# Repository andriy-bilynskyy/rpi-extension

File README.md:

# Raspberry Pi - Radioberry interconnection board

This project is a PCB design to create SDR transceiver using
Raspberry Pi and Radioberry boards. Simple connection of boards
seems incomplete:

- usually LCD Touch screen is used which creates EMI
- touch screen usually requires I2C bus but it's already used on a Raspberry header
- switching on/off requires USB connection - strange for complete inbox design
- no RTC
- complete design requires BMS monitoring but again I2C is already occupied

## Main Features

- Radioberry shield (mainly EMI caused by LCD touchscreen)
- 12V battery power supply (switching converter to 5V USB)
- ON/OFF circuits with indication
- RTC

For design is used KiCad Version 6.0.11

Documentation is available under **doc** folder

Prepared fabrication files under **gerber** folder

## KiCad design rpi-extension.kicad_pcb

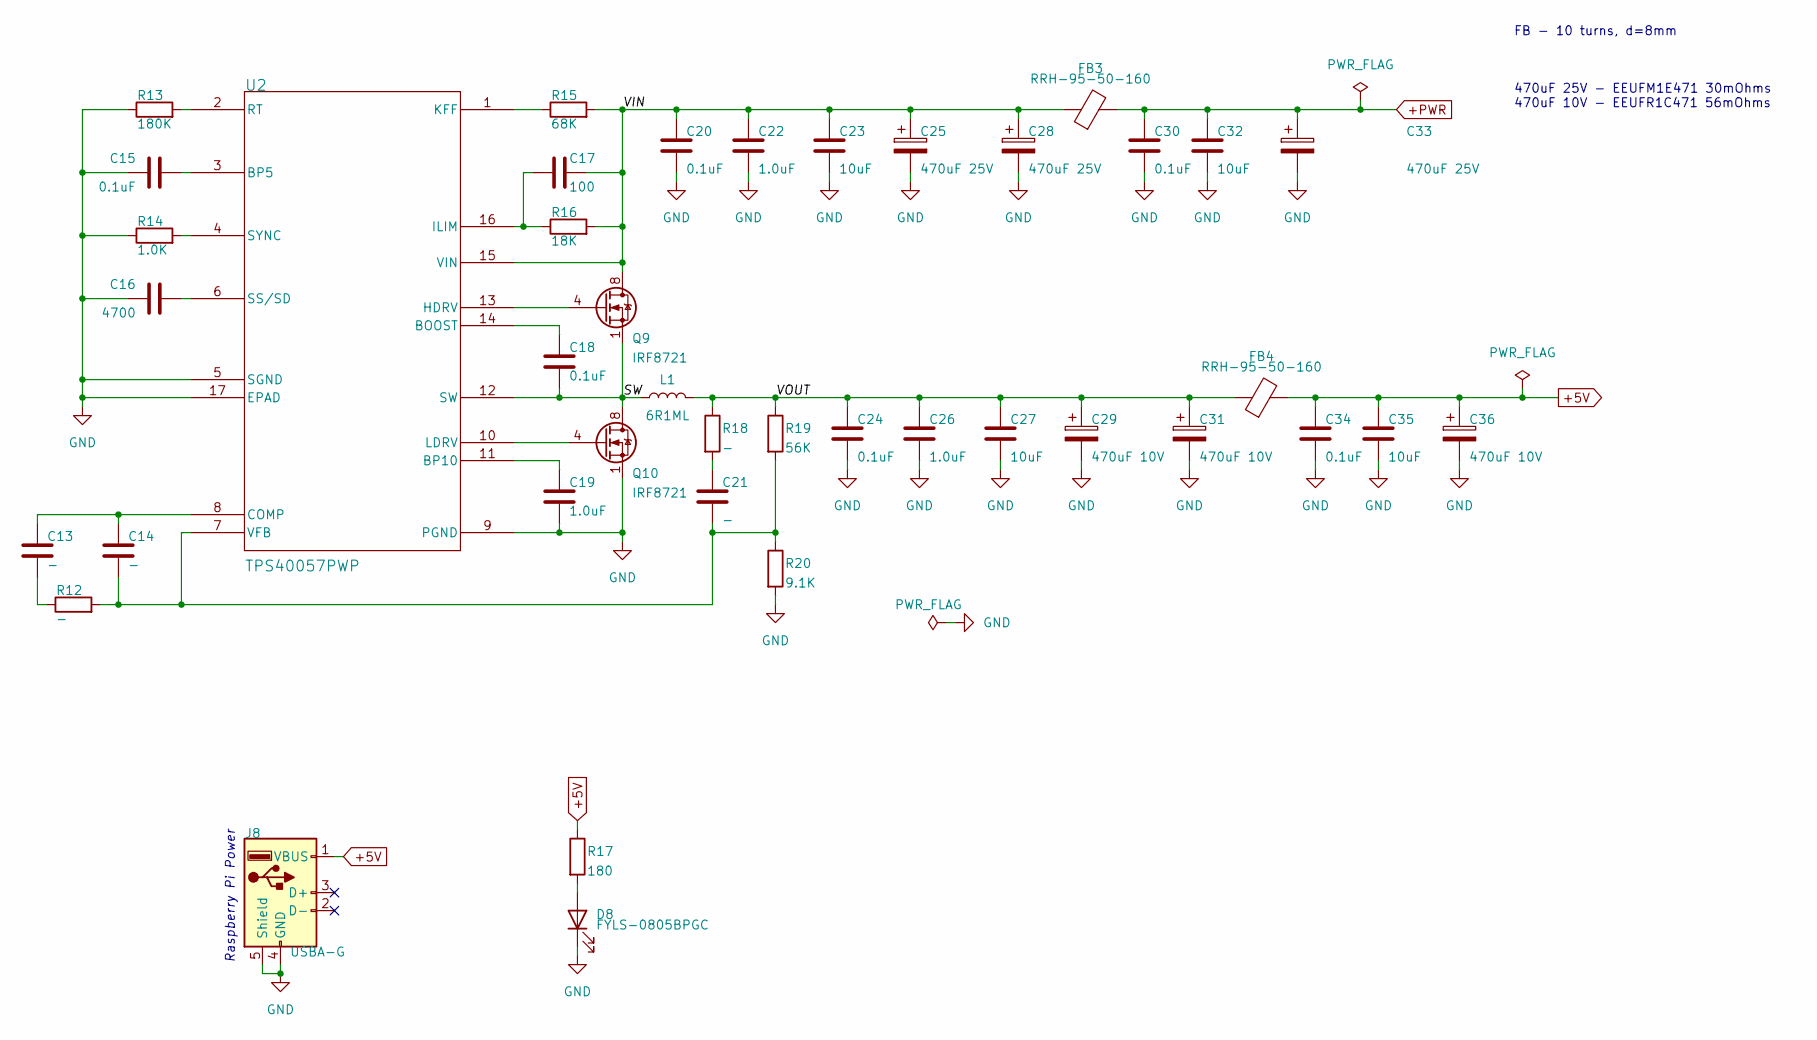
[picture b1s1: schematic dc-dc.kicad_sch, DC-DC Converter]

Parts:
C13, C14, C21: -; C_0805_2012Metric_Pad1.18x1.45mm_HandSolder
C15, C18, C20, C24, C30, C34: 0.1uF; C_0805_2012Metric_Pad1.18x1.45mm_HandSolder
C16: 4700; C_0805_2012Metric_Pad1.18x1.45mm_HandSolder
C17: 100; C_0805_2012Metric_Pad1.18x1.45mm_HandSolder
C19, C22, C26: 1.0uF; C_0805_2012Metric_Pad1.18x1.45mm_HandSolder
C23, C27, C32, C35: 10uF; C_0805_2012Metric_Pad1.18x1.45mm_HandSolder
C25, C28, C33: 470uF 25V; CP_Radial_D10.0mm_P5.00mm
C29, C31, C36: 470uF 10V; CP_Radial_D8.0mm_P3.50mm
D8: FYLS-0805BPGC; LED_0805_2012Metric_Pad1.15x1.40mm_HandSolder
FB3, FB4: RRH-95-50-160; L_Radial_D9.5mm_P5.00mm_Fastron_07HVP
J8: USBA-G; USB_A_Stewart_SS-52100-001_Horizontal
L1: 6R1ML; CDEP147
Q9, Q10: IRF8721; SOIC-8_3.9x4.9mm_P1.27mm
R12, R18: -; R_0805_2012Metric_Pad1.20x1.40mm_HandSolder
R13: 180K; R_0805_2012Metric_Pad1.20x1.40mm_HandSolder
R14: 1.0K; R_0805_2012Metric_Pad1.20x1.40mm_HandSolder
R15: 68K; R_0805_2012Metric_Pad1.20x1.40mm_HandSolder
R16: 18K; R_0805_2012Metric_Pad1.20x1.40mm_HandSolder
R17: 180; R_0805_2012Metric_Pad1.20x1.40mm_HandSolder
R19: 56K; R_0805_2012Metric_Pad1.20x1.40mm_HandSolder
R20: 9.1K; R_0805_2012Metric_Pad1.20x1.40mm_HandSolder
U2: TPS40057PWP; HTSSOP-16-1EP_4.4x5mm_P0.65mm_EP3.4x5mm_Mask2.46x2.31mm_The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

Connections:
+5V: C34.2, C35.2, C36.1, FB4.2, J8.1 (VBUS), R17.1
+PWR: C30.2, C32.2, C33.1, FB3.2; also elsewhere on the board
/DC-DC/SW: C18.1, L1.1, Q9.1 (S), Q9.2 (S), Q9.3 (S), Q10.5 (D), Q10.6 (D), Q10.7 (D), Q10.8 (D), U2.12 (SW)
/DC-DC/VIN: C17.1, C20.2, C22.2, C23.2, C25.1, C28.1, FB3.1, Q9.5 (D), Q9.6 (D), Q9.7 (D), Q9.8 (D), R15.2, R16.2, U2.15 (VIN)
/DC-DC/VOUT: C24.2, C26.2, C27.2, C29.1, C31.1, FB4.1, L1.2, R18.1, R19.1
GND: C15.1, C16.1, C19.1, C20.1, C22.1, C23.1, C24.1, C25.2, C26.1, C27.1, C28.2, C29.2, C30.1, C31.2, C32.1, C33.2, C34.1, C35.1, C36.2, D8.1 (K), J8.4 (GND), J8.5 (Shield), Q10.1 (S), Q10.2 (S), Q10.3 (S), R13.1, R14.1, R20.2, U2.5 (SGND), U2.9 (PGND), U2.17 (EPAD); also elsewhere on the board
unnamed: C13.1, R12.1
unnamed: C13.2, C14.2, U2.8 (COMP)
unnamed: C14.1, C21.1, R12.2, R19.2, R20.1, U2.7 (VFB)
unnamed: C15.2, U2.3 (BP5)
unnamed: C16.2, U2.6 (SS/SD)
unnamed: C17.2, R16.1, U2.16 (ILIM)
unnamed: C18.2, U2.14 (BOOST)
unnamed: C19.2, U2.11 (BP10)
unnamed: C21.2, R18.2
unnamed: D8.2 (A), R17.2
unnamed: Q9.4 (G), U2.13 (HDRV)
unnamed: Q10.4 (G), U2.10 (LDRV)
unnamed: R13.2, U2.2 (RT)
unnamed: R14.2, U2.4 (SYNC)
unnamed: R15.1, U2.1 (KFF)

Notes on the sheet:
470uF 25V - EEUFM1E471 30mOhms 470uF 10V - EEUFR1C471 56mOhms
FB - 10 turns, d=8mm
Raspberry Pi Power

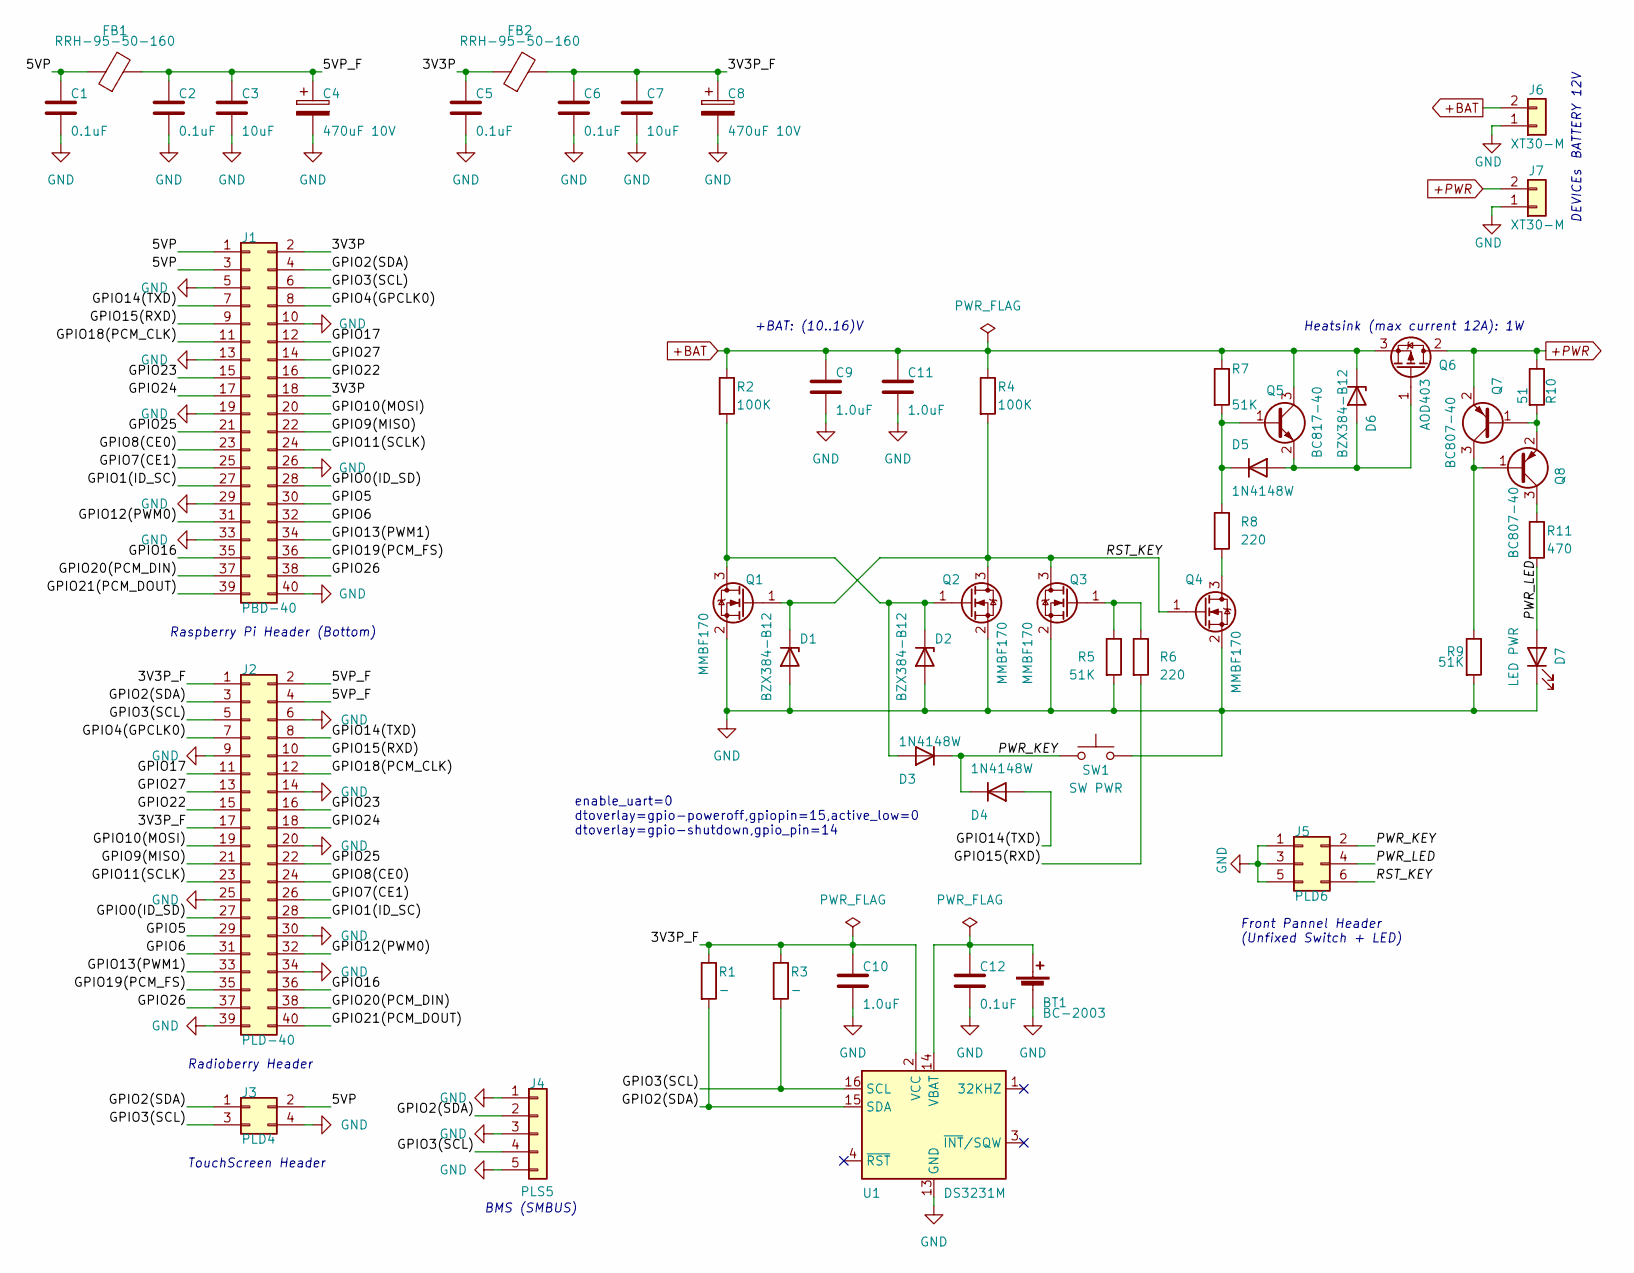
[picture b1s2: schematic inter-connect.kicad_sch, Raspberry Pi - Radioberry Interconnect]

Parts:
BT1: BC-2003; BatteryHolder_MPD_BC2003_1x2032
C1, C2, C5, C6, C12: 0.1uF; C_0805_2012Metric_Pad1.18x1.45mm_HandSolder
C3, C7: 10uF; C_0805_2012Metric_Pad1.18x1.45mm_HandSolder
C4, C8: 470uF 10V; CP_Radial_D8.0mm_P3.50mm
C9, C10, C11: 1.0uF; C_0805_2012Metric_Pad1.18x1.45mm_HandSolder
D1, D2, D6: BZX384-B12; D_SOD-323_HandSoldering
D3, D4, D5: 1N4148W; D_SOD-323_HandSoldering
D7: LED PWR
FB1, FB2: RRH-95-50-160; L_Radial_D9.5mm_P5.00mm_Fastron_07HVP
J1: PBD-40; PinHeader_2x20_P2.54mm_Vertical
J2: PLD-40; PinHeader_2x20_P2.54mm_Vertical
J3: PLD4; PinHeader_2x02_P2.54mm_Vertical
J4: PLS5; PinHeader_1x05_P2.54mm_Vertical
J5: PLD6; PinHeader_2x03_P2.54mm_Vertical
J6, J7: XT30-M; AMASS_XT30U-M_1x02_P5.0mm_Vertical
Q1, Q2, Q3, Q4: MMBF170; SOT-23_Handsoldering
Q5: BC817-40; SOT-23_Handsoldering
Q6: AOD403; TO-252-2
Q7, Q8: BC807-40; SOT-23
R1, R3: -; R_0805_2012Metric_Pad1.20x1.40mm_HandSolder
R2, R4: 100K; R_0805_2012Metric_Pad1.20x1.40mm_HandSolder
R5, R7, R9: 51K; R_0805_2012Metric_Pad1.20x1.40mm_HandSolder
R6, R8: 220; R_0805_2012Metric_Pad1.20x1.40mm_HandSolder
R10: 51; R_0805_2012Metric_Pad1.20x1.40mm_HandSolder
R11: 470; R_0805_2012Metric_Pad1.20x1.40mm_HandSolder
SW1: SW PWR
U1: DS3231M; SOIC-16W_7.5x10.3mm_P1.27mm

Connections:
+BAT: C9.2, C11.2, D6.1 (K), J6.2, Q5.3 (C), Q6.3 (S), R2.1, R4.1, R7.1
+PWR: J7.2, Q6.2 (D), Q7.2 (E), R10.1; also elsewhere on the board
/Inter Connect/3V3P: C5.2, FB2.1, J1.2, J1.18
/Inter Connect/3V3P_F: C6.2, C7.2, C8.1, C10.2, FB2.2, J2.1, J2.17, R1.1, R3.1, U1.2 (VCC)
/Inter Connect/5VP: C1.2, FB1.1, J1.1, J1.3, J3.2
/Inter Connect/5VP_F: C2.2, C3.2, C4.1, FB1.2, J2.2, J2.4
/Inter Connect/GPIO0(ID_SD): J1.28, J2.27
/Inter Connect/GPIO1(ID_SC): J1.27, J2.28
/Inter Connect/GPIO2(SDA): J1.4, J2.3, J3.1, J4.2, R1.2, U1.15 (SDA)
/Inter Connect/GPIO3(SCL): J1.6, J2.5, J3.3, J4.4, R3.2, U1.16 (SCL)
/Inter Connect/GPIO4(GPCLK0): J1.8, J2.7
/Inter Connect/GPIO5: J1.30, J2.29
/Inter Connect/GPIO6: J1.32, J2.31
/Inter Connect/GPIO7(CE1): J1.25, J2.26
/Inter Connect/GPIO8(CE0): J1.23, J2.24
/Inter Connect/GPIO9(MISO): J1.22, J2.21
/Inter Connect/GPIO10(MOSI): J1.20, J2.19
/Inter Connect/GPIO11(SCLK): J1.24, J2.23
/Inter Connect/GPIO12(PWM0): J1.31, J2.32
/Inter Connect/GPIO13(PWM1): J1.34, J2.33
/Inter Connect/GPIO14(TXD): D4.2 (A), J1.7, J2.8
/Inter Connect/GPIO15(RXD): J1.9, J2.10, R6.2
/Inter Connect/GPIO16: J1.35, J2.36
/Inter Connect/GPIO17: J1.12, J2.11
/Inter Connect/GPIO18(PCM_CLK): J1.11, J2.12
/Inter Connect/GPIO19(PCM_FS): J1.36, J2.35
/Inter Connect/GPIO20(PCM_DIN): J1.37, J2.38
/Inter Connect/GPIO21(PCM_DOUT): J1.39, J2.40
/Inter Connect/GPIO22: J1.16, J2.15
/Inter Connect/GPIO23: J1.15, J2.16
/Inter Connect/GPIO24: J1.17, J2.18
/Inter Connect/GPIO25: J1.21, J2.22
/Inter Connect/GPIO26: J1.38, J2.37
/Inter Connect/GPIO27: J1.14, J2.13
/Inter Connect/PWR_KEY: D3.1 (K), D4.1 (K), J5.2, SW1.1
/Inter Connect/PWR_LED: D7.2 (A), J5.4, R11.2
/Inter Connect/RST_KEY: D1.1 (K), J5.6, Q1.1 (G), Q2.3 (D), Q3.3 (D), Q4.1 (G), R4.2
GND: BT1.2 (-), C1.1, C2.1, C3.1, C4.2, C5.1, C6.1, C7.1, C8.2, C9.1, C10.1, C11.1, C12.1, D1.2 (A), D2.2 (A), D7.1 (K), J1.5, J1.10, J1.13, J1.19, J1.26, J1.29, J1.33, J1.40, J2.6, J2.9, J2.14, J2.20, J2.25, J2.30, J2.34, J2.39, J3.4, J4.1, J4.3, J4.5, J5.1, J5.3, J5.5, J6.1, J7.1, Q1.2 (S), Q2.2 (S), Q3.2 (S), Q4.2 (S), R5.2, R9.2, SW1.2, U1.5 (GND), U1.6 (GND), U1.7 (GND), U1.8 (GND), U1.9 (GND), U1.10 (GND), U1.11 (GND), U1.12 (GND), U1.13 (GND); also elsewhere on the board
unnamed: BT1.1 (+), C12.2, U1.14 (VBAT)
unnamed: D2.1 (K), D3.2 (A), Q1.3 (D), Q2.1 (G), R2.2
unnamed: D5.1 (K), Q5.1 (B), R7.2, R8.1
unnamed: D5.2 (A), D6.2 (A), Q5.2 (E), Q6.1 (G)
unnamed: Q3.1 (G), R5.1, R6.1
unnamed: Q4.3 (D), R8.2
unnamed: Q7.1 (B), Q8.2 (E), R10.2
unnamed: Q7.3 (C), Q8.1 (B), R9.1
unnamed: Q8.3 (C), R11.1

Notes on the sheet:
enable_uart=0 dtoverlay=gpio-poweroff,gpiopin=15,active_low=0 dtoverlay=gpio-shutdown,gpio_pin=14
Front Pannel Header (Unfixed Switch + LED)
BATTERY 12V
TouchScreen Header
DEVICEs
+BAT: (10..16)V
Heatsink (max current 12A): 1W
Raspberry Pi Header (Bottom)
Radioberry Header
BMS (SMBUS)

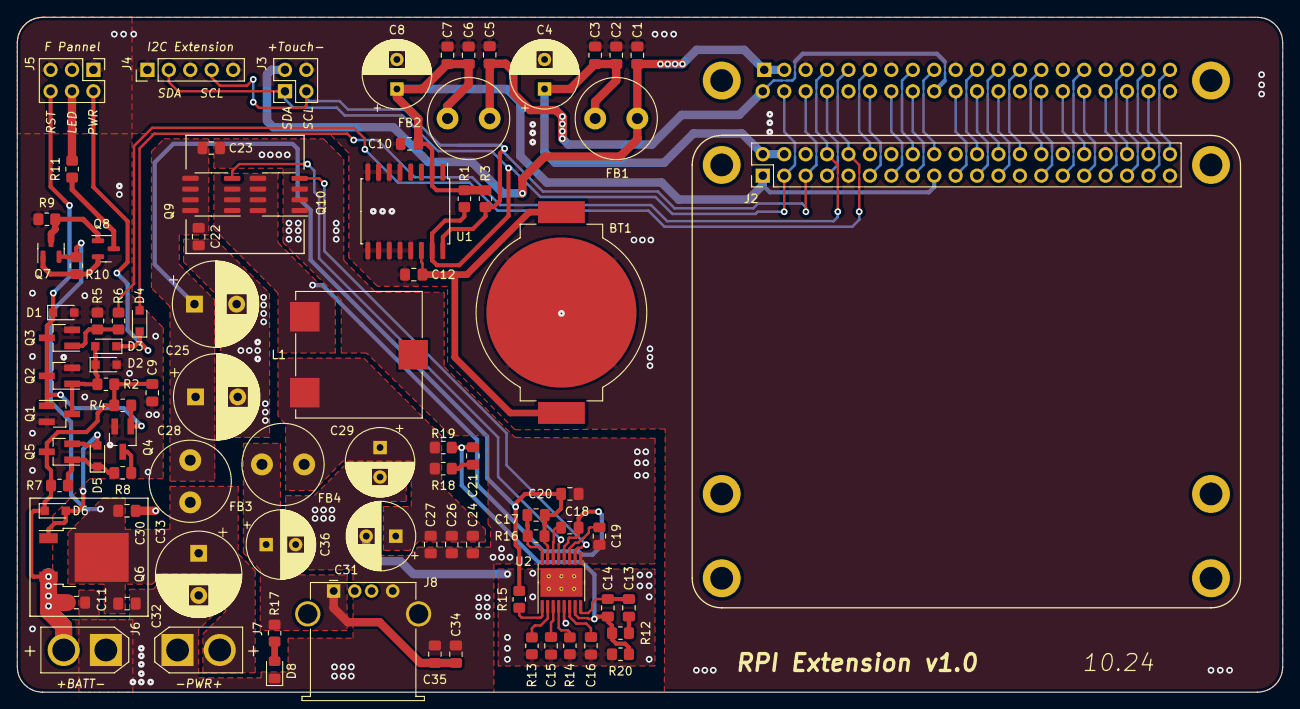
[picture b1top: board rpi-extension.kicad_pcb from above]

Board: 2 copper layers, 150.0 x 80.0 mm, 89 parts (1 on the bottom side), 66 nets.

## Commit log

2024-10-07 Initial commit.
2024-10-07 Add MIT license
2024-10-07 Add readme.
2024-10-07 Add build of materials.
